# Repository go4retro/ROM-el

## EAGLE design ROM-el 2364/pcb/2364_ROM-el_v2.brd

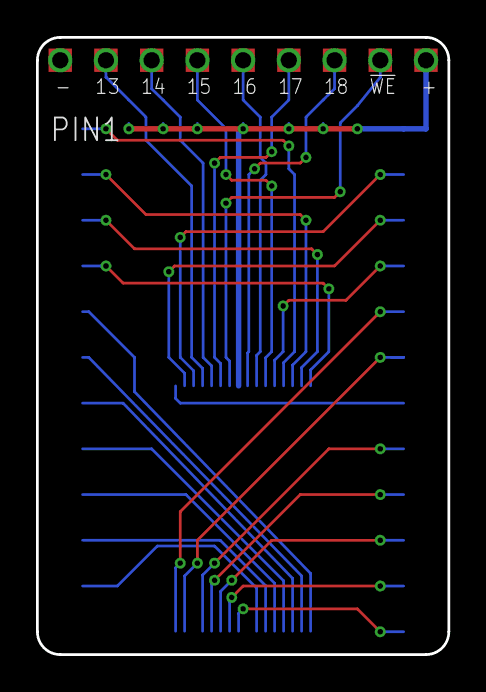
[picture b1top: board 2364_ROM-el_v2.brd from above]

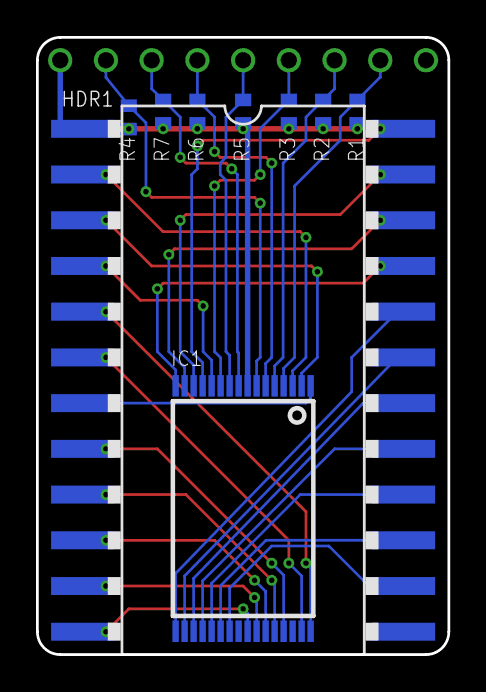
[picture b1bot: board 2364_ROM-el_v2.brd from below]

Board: 2 copper layers, 22.9 x 34.3 mm, 18 parts (8 on the bottom side), 31 nets.

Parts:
13, 14, 15, 16, 17, 18: TPTP13SQ; TP13SQ
!WE: TPTP13SQ; TP13SQ
+: TPTP13SQ; TP13SQ
-: TPTP13SQ; TP13SQ
HDR1: 2364-SB; DIL24-SMD-REVERSE
IC1: VSOP32
R1, R2, R3, R4, R5, R6, R7: R0402

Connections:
!WE: !WE.TP, IC1.7, R4.1
A0: HDR1.8, IC1.20
A1: HDR1.7, IC1.19
A2: HDR1.6, IC1.18
A3: HDR1.5, IC1.17
A4: HDR1.4, IC1.16
A5: HDR1.3, IC1.15
A6: HDR1.2, IC1.14
A7: HDR1.1, IC1.13
A8: HDR1.23, IC1.3
A9: HDR1.22, IC1.2
A10: HDR1.19, IC1.31
A11: HDR1.18, IC1.1
A12: HDR1.21, IC1.12
A13: 13.TP, IC1.4, R1.1
A14: 14.TP, IC1.5, R2.1
A15: 15.TP, IC1.11, R3.1
A16: 16.TP, IC1.10, R5.1
A17: 17.TP, IC1.6, R6.1
A18: 18.TP, IC1.9, R7.1
D0: HDR1.9, IC1.21
D1: HDR1.10, IC1.22
D2: HDR1.11, IC1.23
D3: HDR1.13, IC1.25
D4: HDR1.14, IC1.26
D5: HDR1.15, IC1.27
D6: HDR1.16, IC1.28
D7: HDR1.17, IC1.29
GND: -.TP, HDR1.12, IC1.24, IC1.30
unnamed: HDR1.20, IC1.32
VCC: +.TP, HDR1.24, IC1.8, R1.2, R2.2, R3.2, R4.2, R5.2, R6.2, R7.2

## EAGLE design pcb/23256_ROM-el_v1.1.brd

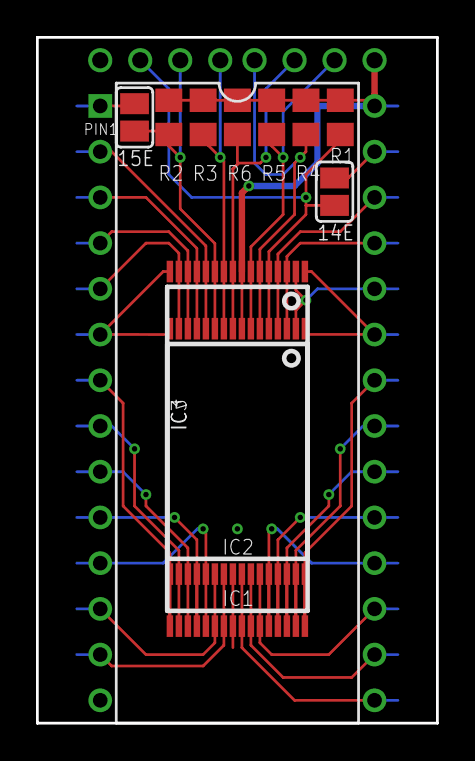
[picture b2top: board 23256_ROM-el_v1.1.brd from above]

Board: 2 copper layers, 22.2 x 38.1 mm, 12 parts (0 on the bottom side), 34 nets.

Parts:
14E: SJ
15E: 15E; SJ
IC1: FLASH_RAM4096KBT; TSOP32
IC2: FLASH_RAM4096KB'V'; VSOP32
IC3: 23128-23512; DIL28-ROUNDPAD
IC4: 23128-23512; DIL28-SMD-REVERSE
R1, R2, R3, R4, R5, R6: R0805

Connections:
!WE: IC1.7, IC2.7, R5.1
A0: IC1.20, IC2.20, IC3.10, IC4.10
A1: IC1.19, IC2.19, IC3.9, IC4.9
A2: IC1.18, IC2.18, IC3.8, IC4.8
A3: IC1.17, IC2.17, IC3.7, IC4.7
A4: IC1.16, IC2.16, IC3.6, IC4.6
A5: IC1.15, IC2.15, IC3.5, IC4.5
A6: IC1.14, IC2.14, IC3.4, IC4.4
A7: IC1.13, IC2.13, IC3.3, IC4.3
A8: IC1.3, IC2.3, IC3.25, IC4.25
A9: IC1.2, IC2.2, IC3.24, IC4.24
A10: IC1.31, IC2.31, IC3.21, IC4.21
A11: IC1.1, IC2.1, IC3.23, IC4.23
A12: IC1.12, IC2.12, IC3.2, IC4.2
A13: IC1.4, IC2.4, IC3.26, IC4.26
A14: 14E.1, IC1.5, IC2.5, R1.1
A15: 15E.1, IC1.11, IC2.11, R2.1
A16: IC1.10, IC2.10, R3.1
A17: IC1.6, IC2.6, R4.1
A18: IC1.9, IC2.9, R6.1
D0: IC1.21, IC2.21, IC3.11, IC4.11
D1: IC1.22, IC2.22, IC3.12, IC4.12
D2: IC1.23, IC2.23, IC3.13, IC4.13
D3: IC1.25, IC2.25, IC3.15, IC4.15
D4: IC1.26, IC2.26, IC3.16, IC4.16
D5: IC1.27, IC2.27, IC3.17, IC4.17
D6: IC1.28, IC2.28, IC3.18, IC4.18
D7: IC1.29, IC2.29, IC3.19, IC4.19
GND: IC1.24, IC2.24, IC3.14, IC4.14
unnamed: IC1.32, IC2.32, IC3.22, IC4.22
unnamed: IC1.30, IC2.30, IC3.20, IC4.20
unnamed: 14E.2, IC3.27, IC4.27
unnamed: 15E.2, IC3.1, IC4.1
VCC: IC1.8, IC2.8, IC3.28, IC4.28, R1.2, R2.2, R3.2, R4.2, R5.2, R6.2

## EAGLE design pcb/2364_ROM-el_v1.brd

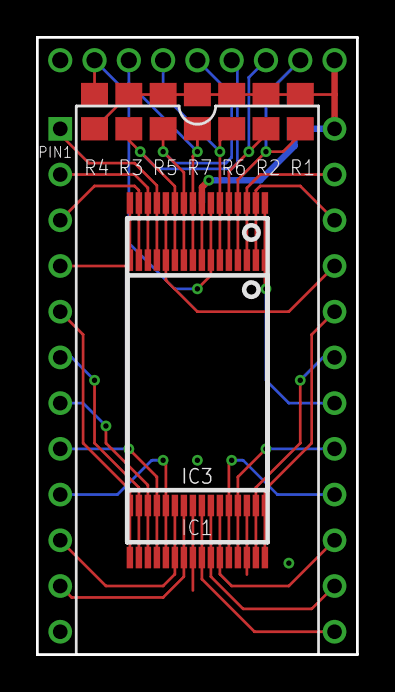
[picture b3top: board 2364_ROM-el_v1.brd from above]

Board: 2 copper layers, 17.8 x 34.3 mm, 10 parts (0 on the bottom side), 31 nets.

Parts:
IC1: TSOP32
IC2: VSOP32
IC3: 2364; DIL24-ROUNDPAD
R1, R2, R3, R4, R5, R6, R7: R0805

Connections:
!WE: IC1.7, IC2.7, R4.1
A0: IC1.20, IC2.20, IC3.8
A1: IC1.19, IC2.19, IC3.7
A2: IC1.18, IC2.18, IC3.6
A3: IC1.17, IC2.17, IC3.5
A4: IC1.16, IC2.16, IC3.4
A5: IC1.15, IC2.15, IC3.3
A6: IC1.14, IC2.14, IC3.2
A7: IC1.13, IC2.13, IC3.1
A8: IC1.3, IC2.3, IC3.23
A9: IC1.2, IC2.2, IC3.22
A10: IC1.31, IC2.31, IC3.19
A11: IC1.1, IC2.1, IC3.18
A12: IC1.12, IC2.12, IC3.21
A13: IC1.4, IC2.4, R1.1
A14: IC1.5, IC2.5, R2.1
A15: IC1.11, IC2.11, R3.1
A16: IC1.10, IC2.10, R5.1
A17: IC1.6, IC2.6, R6.1
A18: IC1.9, IC2.9, R7.1
D0: IC1.21, IC2.21, IC3.9
D1: IC1.22, IC2.22, IC3.10
D2: IC1.23, IC2.23, IC3.11
D3: IC1.25, IC2.25, IC3.13
D4: IC1.26, IC2.26, IC3.14
D5: IC1.27, IC2.27, IC3.15
D6: IC1.28, IC2.28, IC3.16
D7: IC1.29, IC2.29, IC3.17
GND: IC1.24, IC1.30, IC2.24, IC2.30, IC3.12
unnamed: IC1.32, IC2.32, IC3.20
VCC: IC1.8, IC2.8, IC3.24, R1.2, R2.2, R3.2, R4.2, R5.2, R6.2, R7.2

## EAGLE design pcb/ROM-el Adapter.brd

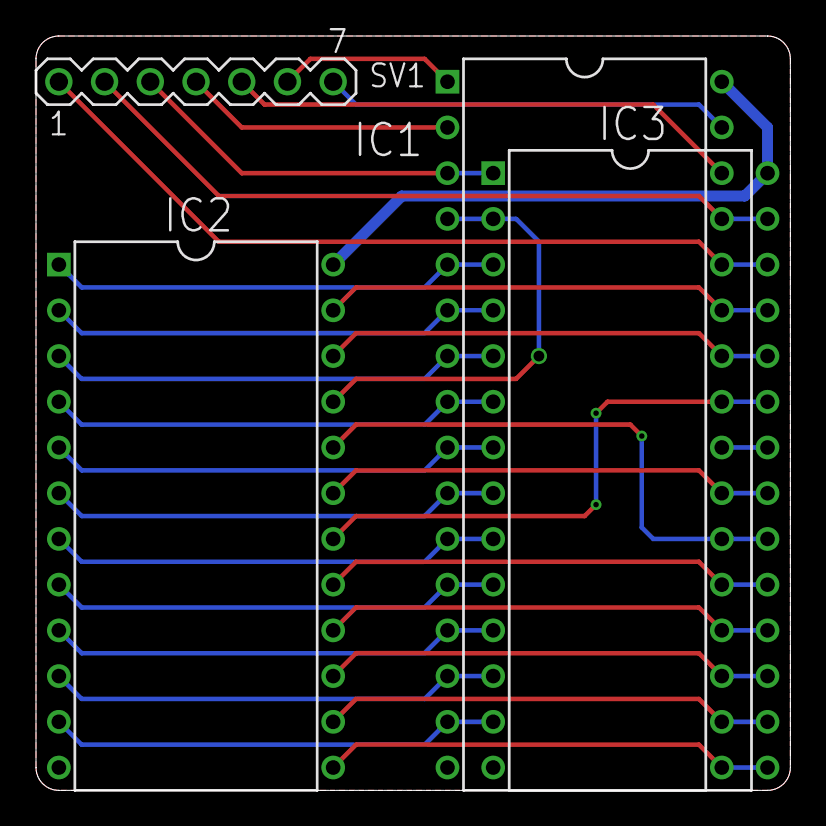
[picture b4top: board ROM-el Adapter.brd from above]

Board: 2 copper layers, 41.9 x 41.9 mm, 4 parts (0 on the bottom side), 32 nets.

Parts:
IC1: AT49F00X; DIL32-RP
IC2: 2364-RP; DIL24-ROUNDPAD
IC3: 23512-RP; DIL28-ROUNDPAD
SV1: MA07-1

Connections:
!CE: IC1.22, IC2.20, IC3.20
!OE: IC1.24, IC3.22
!WE: IC1.31, SV1.7
A0: IC1.12, IC2.8, IC3.10
A1: IC1.11, IC2.7, IC3.9
A2: IC1.10, IC2.6, IC3.8
A3: IC1.9, IC2.5, IC3.7
A4: IC1.8, IC2.4, IC3.6
A5: IC1.7, IC2.3, IC3.5
A6: IC1.6, IC2.2, IC3.4
A7: IC1.5, IC2.1, IC3.3
A8: IC1.27, IC2.23, IC3.25
A9: IC1.26, IC2.22, IC3.24
A10: IC1.23, IC2.19, IC3.21
A11: IC1.25, IC2.18, IC3.23
A12: IC1.4, IC2.21, IC3.2
A13: IC1.28, IC3.26, SV1.1
A14: IC1.29, IC3.27, SV1.2
A15: IC1.3, IC3.1, SV1.3
A16: IC1.2, SV1.4
A17: IC1.30, SV1.5
A18: IC1.1, SV1.6
D0: IC1.13, IC2.9, IC3.11
D1: IC1.14, IC2.10, IC3.12
D2: IC1.15, IC2.11, IC3.13
D3: IC1.17, IC2.13, IC3.15
D4: IC1.18, IC2.14, IC3.16
D5: IC1.19, IC2.15, IC3.17
D6: IC1.20, IC2.16, IC3.18
D7: IC1.21, IC2.17, IC3.19
GND: IC1.16, IC2.12, IC3.14
VCC: IC1.32, IC2.24, IC3.28

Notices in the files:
ROM-el 2364/pcb/2364_ROM-el_v2.brd:
(c)2009-19 RETRO Innovations
pcb/23256_ROM-el_v1.1.brd:
(c)2009-11 RETRO Innovations
pcb/2364_ROM-el_v1.brd:
(c)2009-17 RETRO Innovations
